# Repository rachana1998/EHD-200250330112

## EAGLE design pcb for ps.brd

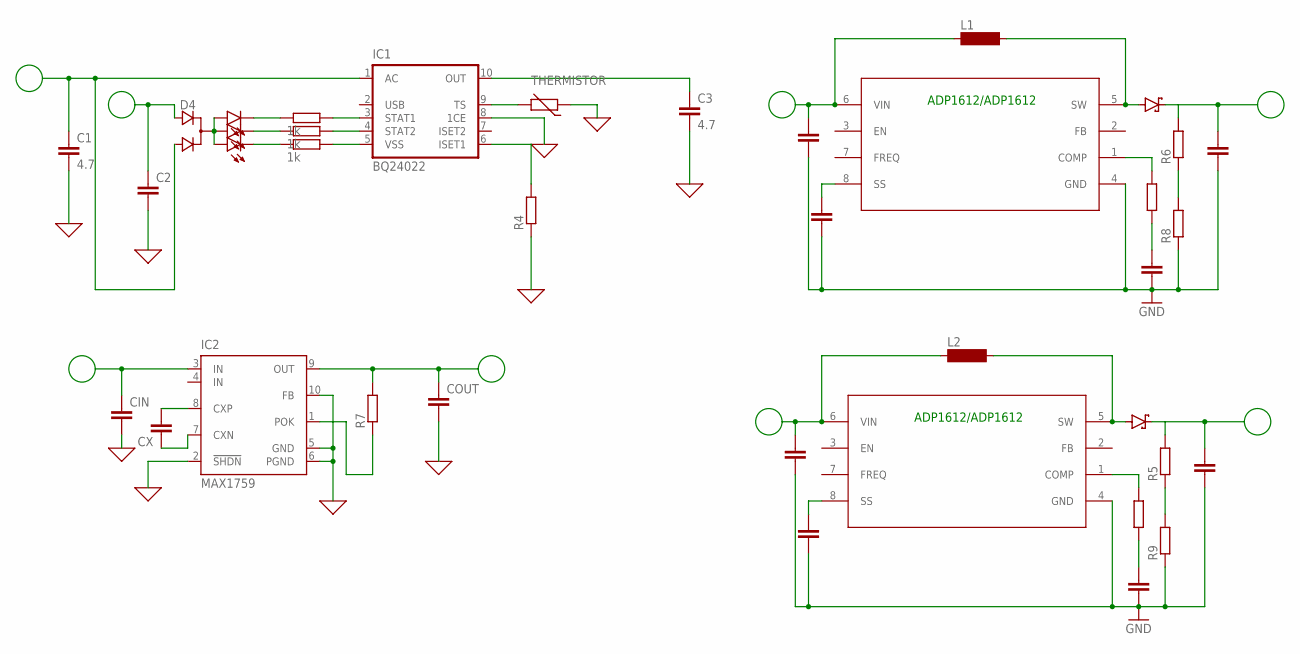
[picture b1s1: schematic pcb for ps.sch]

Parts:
C1, C3: 4.7; C2.5-3
C2, C4, C5, C6, C7: C2,5-3; C2.5-3
CIN: C2,5-3; C2.5-3
COUT: C2,5-3; C2.5-3
CSS, CSS1: C2,5-3; C2.5-3
CX: C2,5-3; C2.5-3
D1, D2, D3: SFH482
D4: D_2ASOT23; SOT-23
D5, D6: BAS40; SOT23
IC1: BQ24022; DRC-S-PVSON-N10
IC2: MAX1759; UMAX10
IN, IN1: C2,5-3; C2.5-3
L1, L2: BS11
R1, R2, R3: 1k; 0204V
R4, R5, R6, R7, R8, R9: R-EU_0204/2V; 0204V
RCOMP, RCOMP1: R-EU_0204/2V; 0204V
THERMISTOR: THERMISTOR_R-2,5; RS-2,5
U1, U2: ADP1612; RM_8_ADI

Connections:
0: CIN.2, COUT.2, IC2.2 (!SHDN), IC2.5 (GND), IC2.6 (PGND), IC2.10 (FB)
GND: C4.2, C5.2, C6.2, C7.2, CSS.2, CSS1.2, IN.2, IN1.2, R8.1, R9.1, U1.4 (GND), U2.4 (GND)
unnamed: C1.1, D4.3 (A2), IC1.1 (AC)
unnamed: C2.1, D4.2 (A1)
unnamed: D1.A, D2.A, D3.A, D4.1 (C)
unnamed: D1.K (C), R1.1
unnamed: D2.K (C), R2.1
unnamed: D3.K (C), R3.1
unnamed: IC1.3 (STAT1), R1.2
unnamed: IC1.4 (STAT2), R2.2
unnamed: IC1.5 (VSS), R3.2
unnamed: IC1.9 (TS), THERMISTOR.2
unnamed: IN.1, L1.1, U1.6 (VIN)
unnamed: D5.1 (A), L1.2, U1.5 (SW)
unnamed: IC1.6 (ISET1), R4.2
unnamed: C3.1, IC1.10 (OUT)
unnamed: IN1.1, L2.1, U2.6 (VIN)
unnamed: C6.1, RCOMP.1
unnamed: RCOMP.2, U1.1 (COMP)
unnamed: CSS.1, U1.8 (SS)
unnamed: C7.1, D5.3 (C)
unnamed: R6.1, R8.2
unnamed: D6.1 (A), L2.2, U2.5 (SW)
unnamed: CIN.1, IC2.3 (IN)
unnamed: CX.2, IC2.8 (CXP)
unnamed: CX.1, IC2.7 (CXN)
unnamed: COUT.1, IC2.9 (OUT), R7.2
unnamed: IC2.1 (POK), R7.1
unnamed: C4.1, RCOMP1.1
unnamed: RCOMP1.2, U2.1 (COMP)
unnamed: CSS1.1, U2.8 (SS)
unnamed: C5.1, D6.3 (C)
unnamed: R5.1, R9.2
THERMISTOR: C1.2, C2.2, C3.2, IC1.8 (1CE), R4.1, THERMISTOR.1

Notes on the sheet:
ADP1612/ADP1612

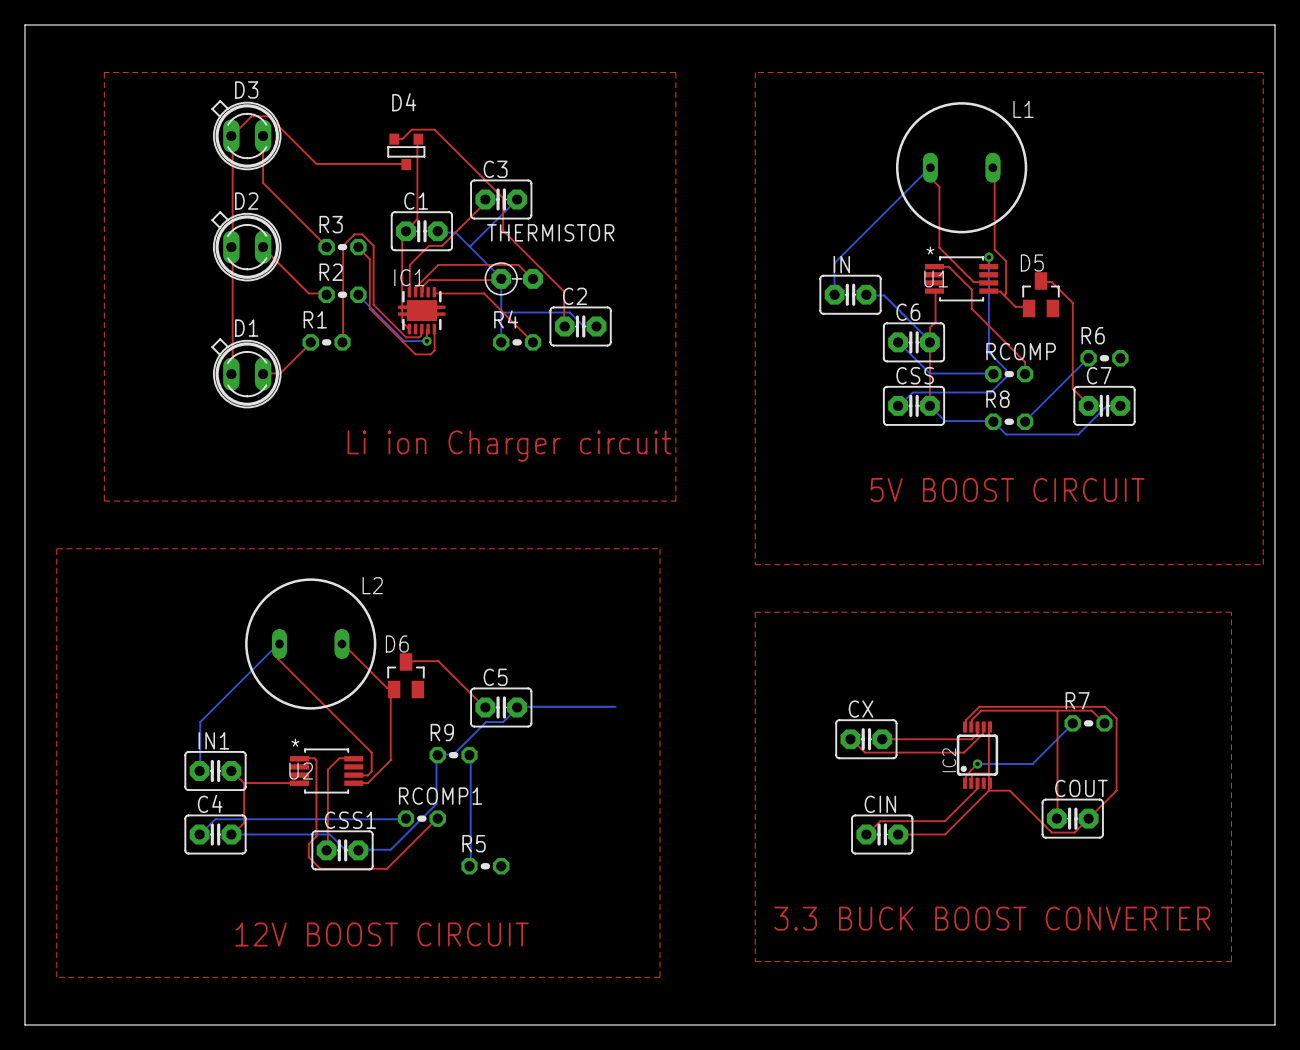
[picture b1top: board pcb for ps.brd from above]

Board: 2 copper layers, 100.0 x 80.0 mm, 38 parts (0 on the bottom side), 34 nets.

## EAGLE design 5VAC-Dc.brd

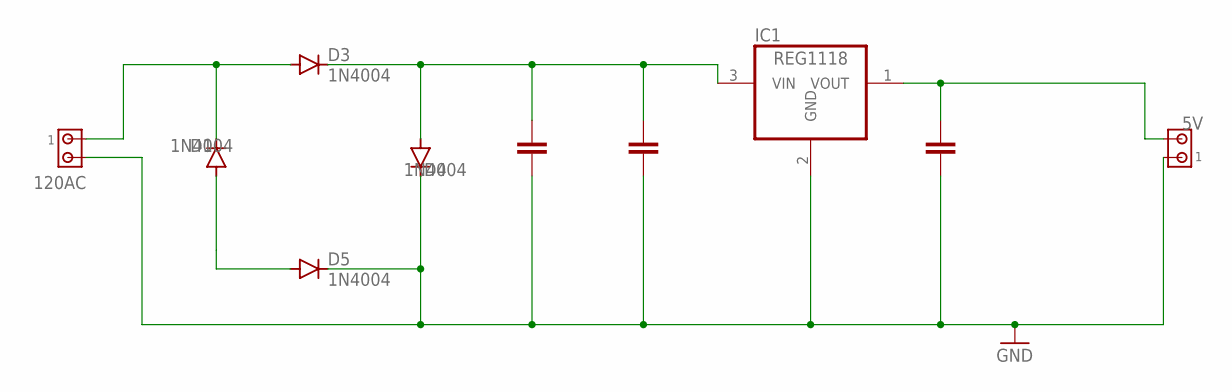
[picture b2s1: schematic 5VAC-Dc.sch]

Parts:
5V: 1445055-2
D1, D3, D4, D5: 1N4004; DO41-10
IC1: REG1118; SOT223
J1: 120AC; 1445055-2

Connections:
GND: 5V.1, D4.C, D5.C, IC1.2 (GND), J1.2
unnamed: D1.C, D3.A, J1.1
unnamed: D1.A, D5.A
unnamed: D3.C, D4.A, IC1.3 (VIN)
unnamed: 5V.2, IC1.1 (VOUT)

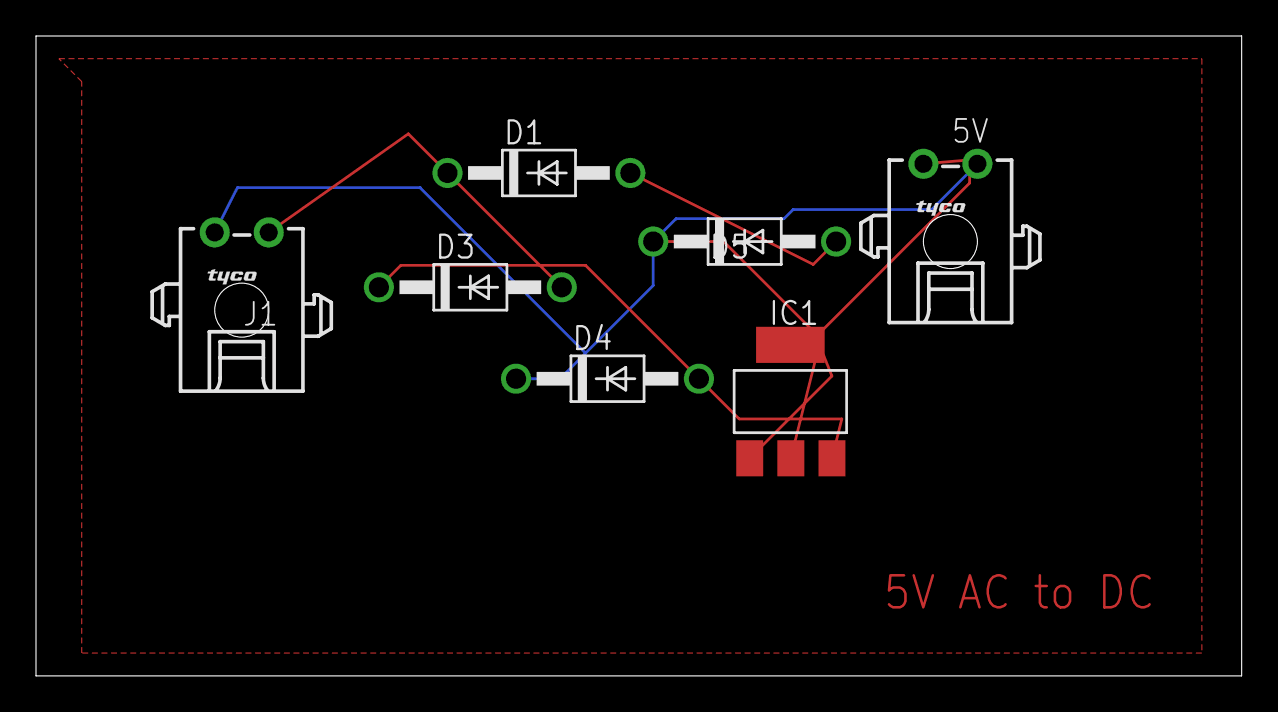
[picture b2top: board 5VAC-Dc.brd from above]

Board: 2 copper layers, 67.0 x 35.6 mm, 7 parts (0 on the bottom side), 5 nets.

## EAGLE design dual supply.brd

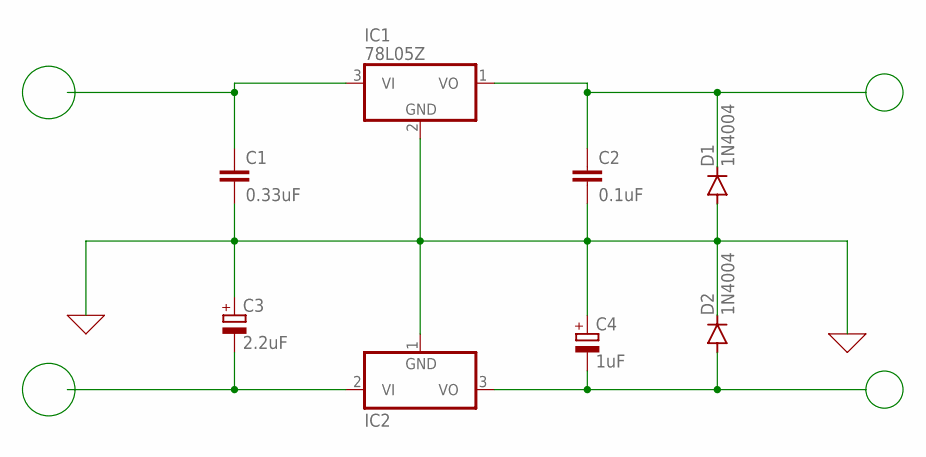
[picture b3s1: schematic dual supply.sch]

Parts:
C1: 0.33uF; C2.5-3
C2: 0.1uF; C2.5-3
C3: 2.2uF; 085CS_1AR
C4: 1uF; 085CS_1AR
D1, D2: 1N4004; DO41-10
IC1: 78L05Z; TO92
IC2: 79L05Z; TO92

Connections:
0: C1.2, C2.2, C3.+, C4.+, D1.A, D2.C, IC1.2 (GND), IC2.1 (GND)
unnamed: C2.1, D1.C, IC1.1 (VO)
unnamed: C1.1, IC1.3 (VI)
unnamed: C4.-, D2.A, IC2.3 (VO)
unnamed: C3.-, IC2.2 (VI)

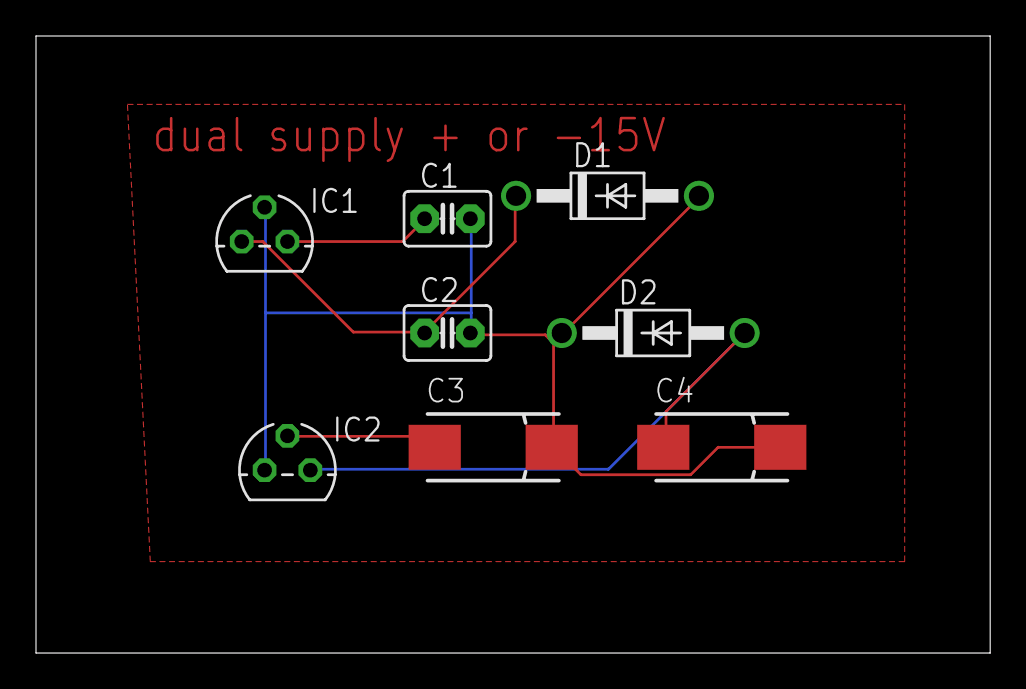
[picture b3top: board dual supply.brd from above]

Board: 2 copper layers, 53.0 x 34.3 mm, 8 parts (0 on the bottom side), 5 nets.
